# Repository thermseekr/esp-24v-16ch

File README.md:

# eumesmo-io-24v16ch
ESP32 based board with 16x optoisolated 24 VDC active high inputs, and 16x open collector 24 VDC outputs.

The outputs are based on the MMBT2222A SMD transistor and are rated for a maximum of 500mA, although it is recommended to limit the current to 350 mA for continous operation. If driving inductive loads like relays, a freewheeling diode or a snubber circuit should be used to limit the switching transients and protect the transistors.

Also included is a 1-Wire interface for external sensors. This interface can be switched to connect either to GPIO16 for use with a bitbang driver like the one available in Tasmota, or to a DS2482S-100 1-Wire master for building more complex networks. Selection is made via SW2, according to the description printed on the PCB. **Attention:** only one dip-switch can be on at any given time.

The board is compatible with the SP7 DIN rail system from [Metaltex](https://www.metaltex.com.br/).

## Hardware Specifications

| Feature | Specification |
| :--- | :--- |
| **Microcontroller** | ESP32-WROOM-32UE-N16 (16MB flash) |
| **Inputs** | 16x 24VDC (optoisolated, active high) |
| **Outputs** | 16x 24VDC (open collector, 350mA cont. / 500mA peak) |
| **Peripherals** | 1-Wire Interface, GPIO or 1-Wire master |
| **Form Factor** | Metaltex DIN Rail Compatible |

## VERSION HISTORY

V6.3 - 2026/07/02 - Added CPU health LED.

V6.2 - 2026/06/13 - Repository renamed from ESP-24V-16CH to eumesmo-io-24v16ch to align the design with the **eumesmo** line of building automation products.

V6.1 - 2026/06/09 - Added voltage monitors for the reset pins on the ESP32 and LAN8710A, replacing the RC circuits. The idea is to get more reliability on the power up sequence with a more controlled reset scheme and a sharper edge on the reset signal. For the ESP32 a TPS3820-33 was selected, which has a reset delay of 25ms. The LAN8710A received a TPS3823-33 with a 200ms delay. The sequence is: ESP32 gets power and goes out of reset 25ms after power good is detected at the 3V3 rail. After boot GPIO12 will go high enabling the 3V3LAN power rail and feeding power to both LAN8710A and TPS3823-33. Then, 200ms after power good is detected on the 3V3LAN rail, the LAN8710A will go out of reset and the power sequence is completed.

V6.0 - 2026/06/06 - The ESP32 was repositioned to allow for better routing to/from the PHY. Test points and a shunt resistor on the 5V rail were added to be used during tests. Will be remove in later versions. A separate GND plane and connector for optocouplers inputs was included. New ethernet connector, with tab up for easier integration with DIN holders from Metaltex. Connectors were replaced for 3.5mm pitch versions for easier wiring installation in the field. The board had to grow 10mm to accomodate these. SMD capacitor sizes were revised for better performance. Transistor base current for the ouputs was increased from 2,3mA to 5,5mA to ensure better saturation. Now, higher loads can be driven without the risk of putting the transistor in the active region. The MCP23017 expander for the inputs was replaced by 2x MCP23008 to avoid the infamous MCP23017 input bug. Rpacks were replaced for individual resistors for more flexible layout. Talking about layout, it was fully revised with better impedance matching for LAN8710 Tx/Rx signal traces. At last, the loads for 3V3A and 3V3LAN rails were revised.

V5.2 - 2026/02/10 - Pins GPA7 and GPB7 of the input MCP23017 were disabled as recommended by Microchip. Inputs 1 and 2 were assigned to GPIO34 and GPIO35 on the ESP32. The mentioned pins were pulled down to 0V and disabled on the mcp23x.dat template. Templates and GPIO assignment information on the schematics were updated.

V5.1 - Corrected footprint of R7 and repositioned the RESET switch as noted by [@yvkoch](https://github.com/yvkoch). Thanks Yrjö! Improved the 1-Wire bus interface aiming for cable runs up to 50m, still to be tested. Also included the option to connect a GPIO to the 1-Wire bus. ATENTION, SW2 can only have one switch ON at any given time, to connect either the DS2482 or GPIO16 to the 1-Wire bus.

V5.0 - Removed the onboard temperature sensor, too sensitive to be on a PCB and also measure the ambient temperature inside the cabinet. Even with cuts around the sensor, it was better at measuring each transistor's influence on the PCB's temperature than the temperature of the environment. Replaced the analog NTC inputs for a 1-Wire i2c interface. Mixing analog and digital circuits on a PCB requires more testing and developing time than I have available. So, fully digital we go. Decreased the brightness of the LEDs, maybe this time I'll get them right :) Repositioned components and rerouted the whole board following the valuable insights taken from [Phil's Lab](https://github.com/pms67) latest videos about Kicad. Thank you very much, Phil.

V4.1 - Redesigned NTC inputs for using differential mode for better immunity against noise. Also the low pass filters were redesigned, the original ones were pretty much useless for any cable larger that 2 meters.

V4.0 - Redesigned digital inputs for better tolerance to long cable runs in noisy environment. Removed pads for NTC inputs 3 and 4, tied them to GND.

V3.2 - Added 4 NTC inputs using an ADS1115 A/D converter with i2c. Reduced current on the LEDs, brightness was too high. Added series resistor and rerouted clock track for better impedance and ring control. Rerouted TX/RX and SCL/SDA tracks for improved signal quality. Layers reordered so the ground plane is directly below the top layer. Returned ESP32 to 16MB version.

V3.1 - Added AHT20 onboard temperature and humidity sensor for cabinet environment monitoring. Replaced ESP32 16MB for 4MB because no stock at JLCPCB.

V3 - Power LED moved to 5V bus. Individual resistors replaced for rpacks where applicable. Moved from 2 to 4 layers, board reduced 30mm in lenght. USB connector repositioned and replaced for horizontal version.

V2 - All GPIOs moved to MCP23017 expanders. MCP interrupt pins connected to GPIOs on the ESP32. USB connector changed for USB type C.

V1 - Initial version, not released. The first 8 inputs used native ESP32 GPIOs, other inputs and all outputs were wired through MCP GPIO expanders.

## LICENSE

This project is licensed under the [Creative Commons BY-NC 4.0 License](https://creativecommons.org/licenses/by-nc/4.0/).
Commercial use is not permitted without prior written consent. See the [LICENSE.txt](LICENSE.txt) file for details.

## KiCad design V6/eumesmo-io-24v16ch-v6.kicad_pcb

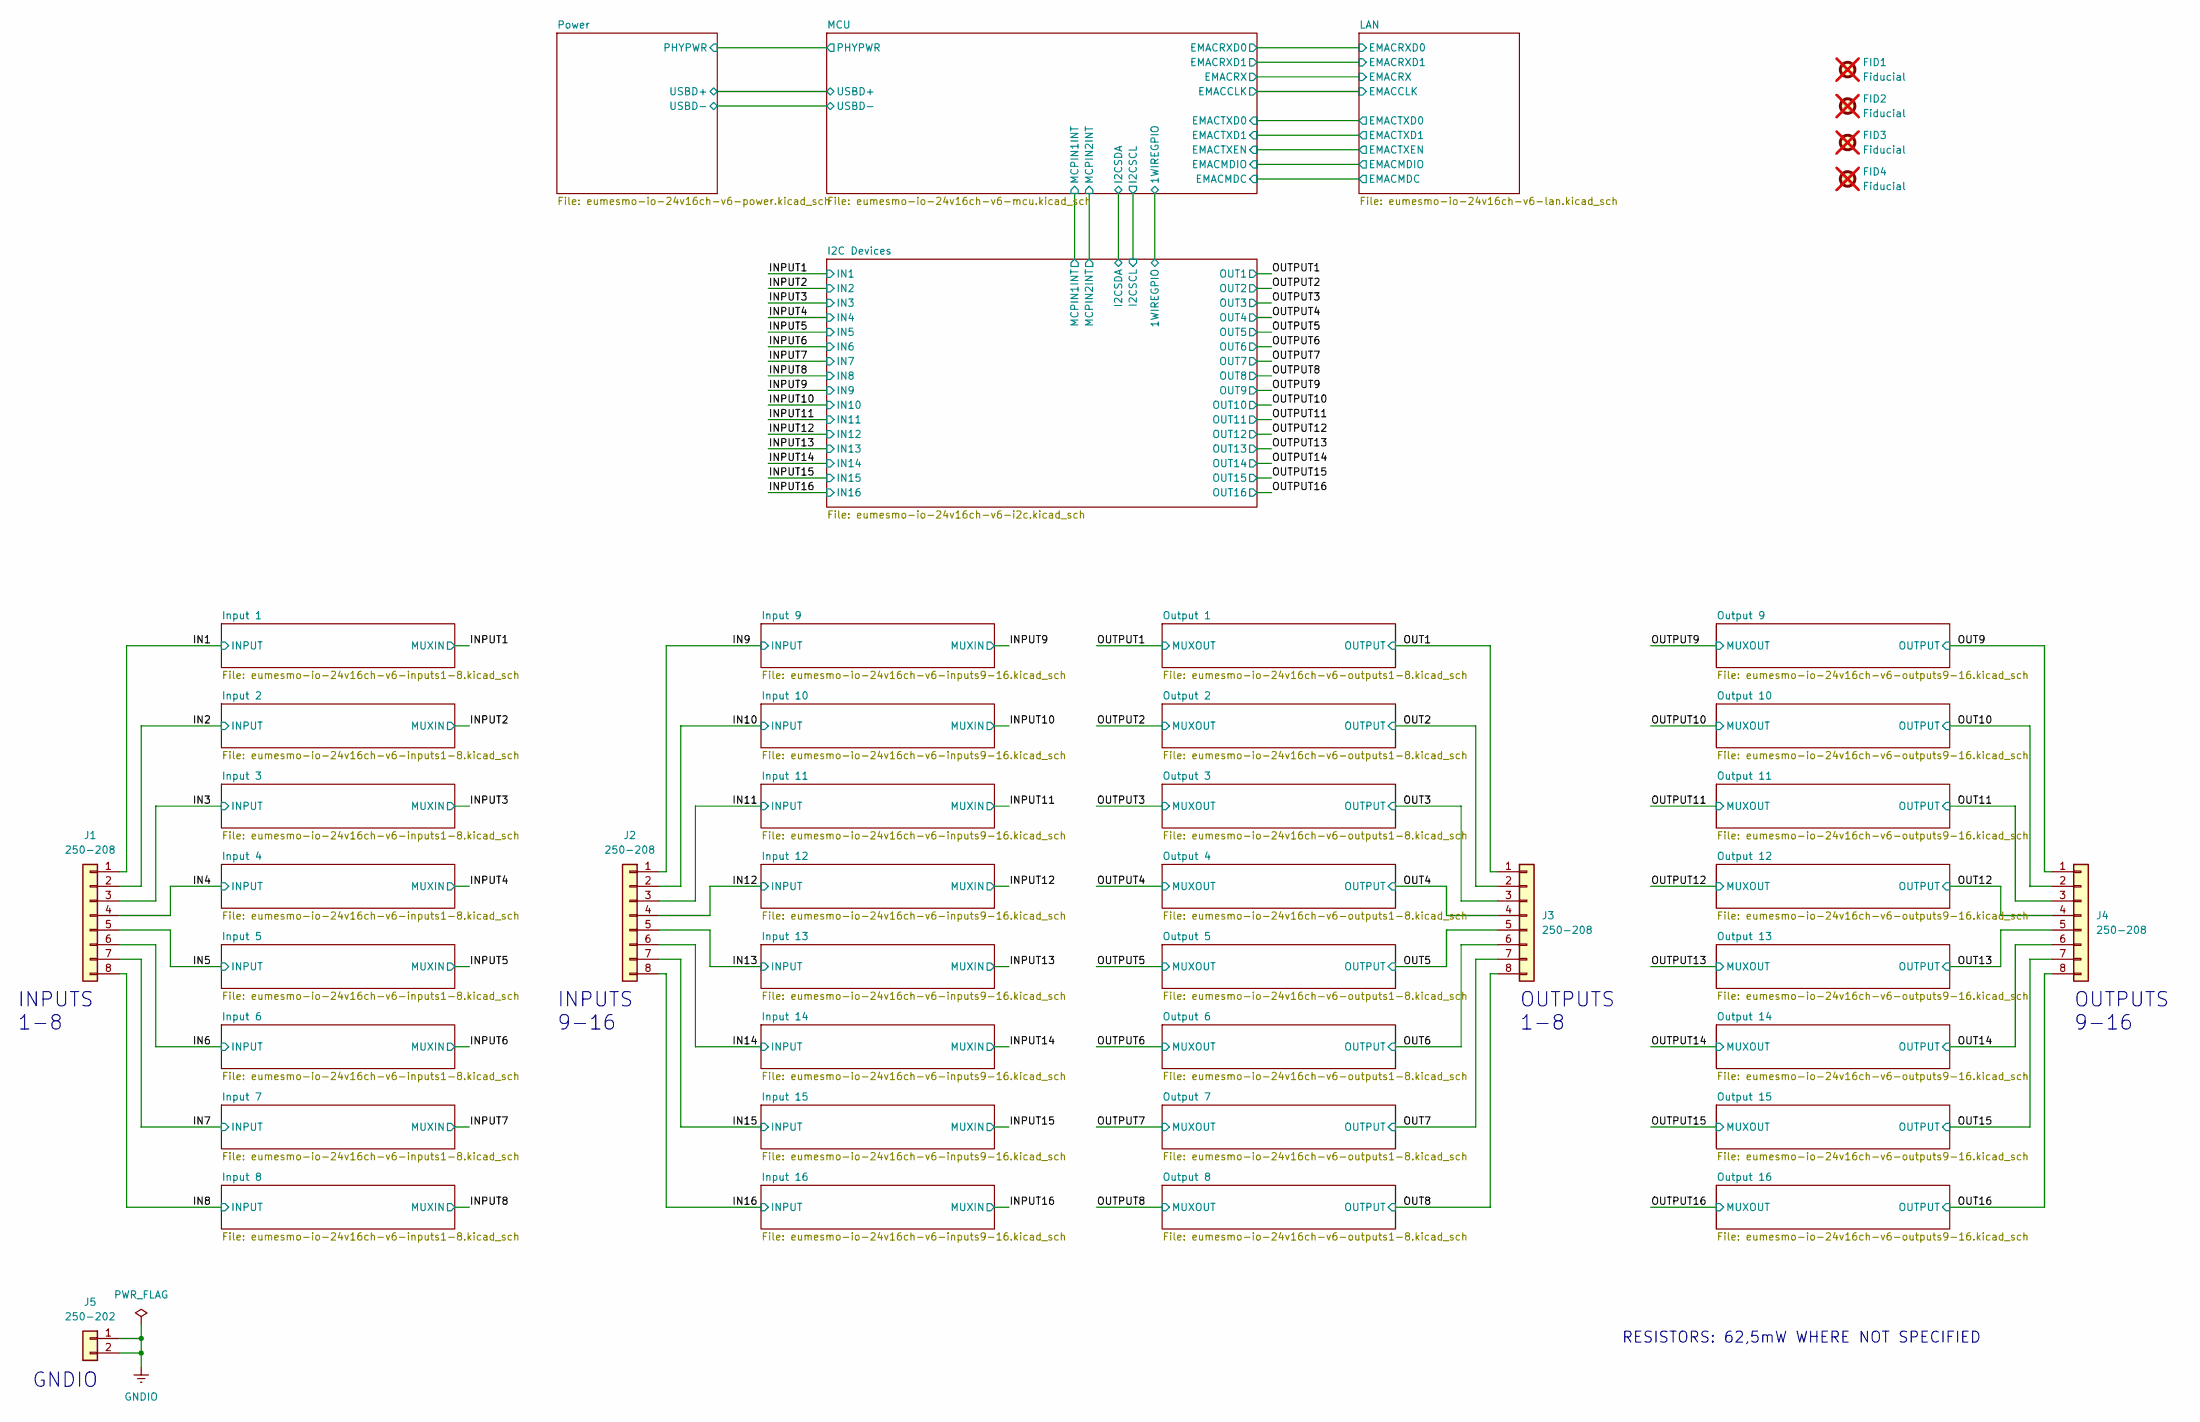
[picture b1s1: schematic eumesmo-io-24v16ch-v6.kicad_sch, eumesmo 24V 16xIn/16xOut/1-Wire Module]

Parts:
FID1, FID2, FID3, FID4: Fiducial; Fiducial_1mm_Mask2mm; not fitted
J1, J2, J3, J4: 250-208; TerminalBlock_Wago_250-208_1x08_P3.5mm_45Degree; Mfr PN 250-208; LCSC Part # C2833587
J5: 250-202; TerminalBlock_Wago_250-202_1x02_P3.5mm_45Degree; Mfr PN 250-202; LCSC Part # C2765061

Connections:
/IN1: J1.1; also elsewhere on the board
/IN2: J1.2; also elsewhere on the board
/IN3: J1.3; also elsewhere on the board
/IN4: J1.4; also elsewhere on the board
/IN5: J1.5; also elsewhere on the board
/IN6: J1.6; also elsewhere on the board
/IN7: J1.7; also elsewhere on the board
/IN8: J1.8; also elsewhere on the board
/IN9: J2.1; also elsewhere on the board
/IN10: J2.2; also elsewhere on the board
/IN11: J2.3; also elsewhere on the board
/IN12: J2.4; also elsewhere on the board
/IN13: J2.5; also elsewhere on the board
/IN14: J2.6; also elsewhere on the board
/IN15: J2.7; also elsewhere on the board
/IN16: J2.8; also elsewhere on the board
/OUT1: J3.1; also elsewhere on the board
/OUT2: J3.2; also elsewhere on the board
/OUT3: J3.3; also elsewhere on the board
/OUT4: J3.4; also elsewhere on the board
/OUT5: J3.5; also elsewhere on the board
/OUT6: J3.6; also elsewhere on the board
/OUT7: J3.7; also elsewhere on the board
/OUT8: J3.8; also elsewhere on the board
/OUT9: J4.1; also elsewhere on the board
/OUT10: J4.2; also elsewhere on the board
/OUT11: J4.3; also elsewhere on the board
/OUT12: J4.4; also elsewhere on the board
/OUT13: J4.5; also elsewhere on the board
/OUT14: J4.6; also elsewhere on the board
/OUT15: J4.7; also elsewhere on the board
/OUT16: J4.8; also elsewhere on the board
GNDIO: J5.1, J5.2; also elsewhere on the board

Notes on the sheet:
OUTPUTS 1-8
OUTPUTS 9-16
RESISTORS: 62,5mW WHERE NOT SPECIFIED
INPUTS 1-8
GNDIO
INPUTS 9-16

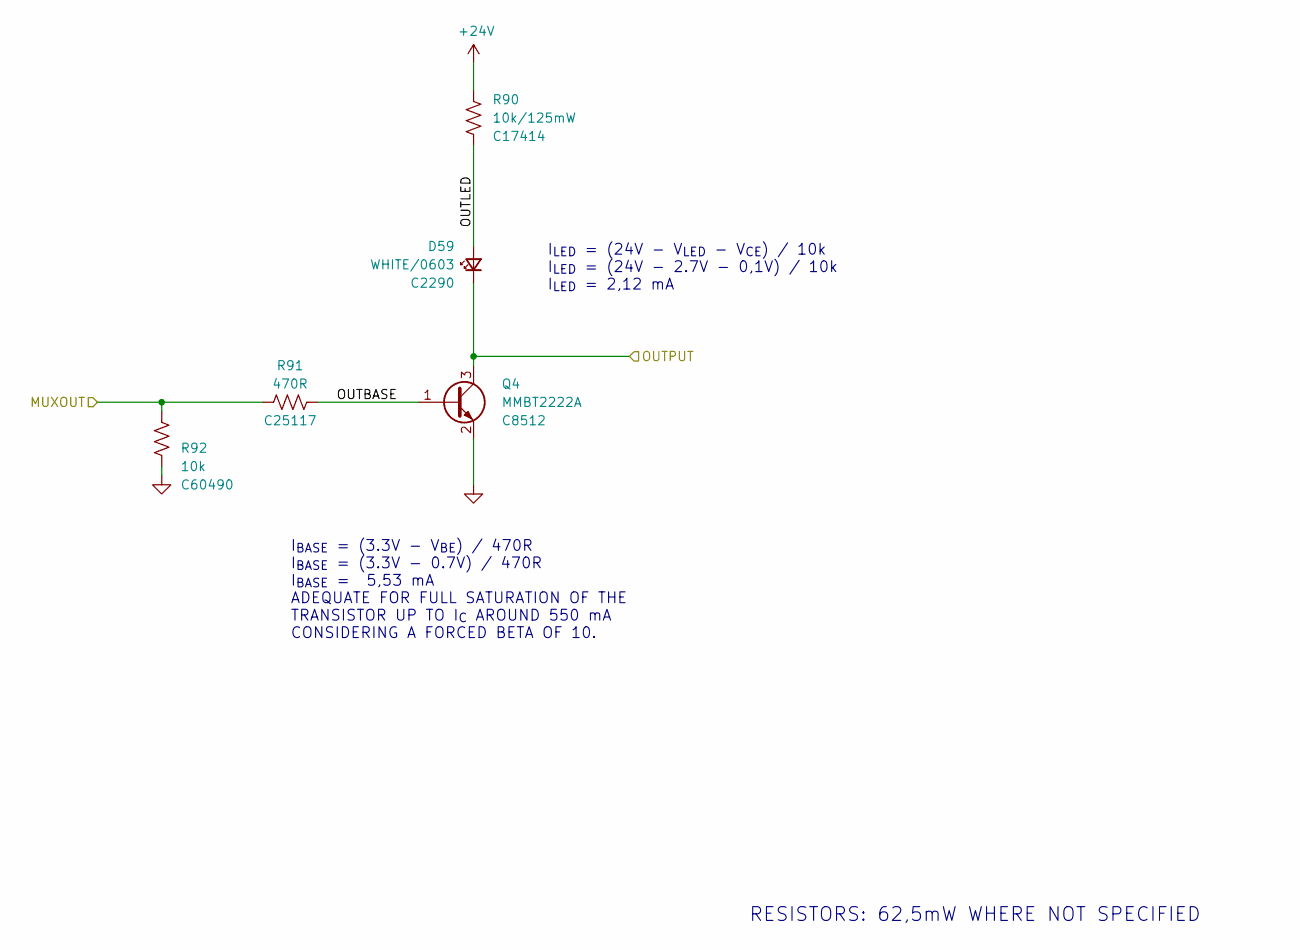
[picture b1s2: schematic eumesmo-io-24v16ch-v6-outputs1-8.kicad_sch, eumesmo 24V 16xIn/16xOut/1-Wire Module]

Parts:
D59: WHITE/0603; LED_0603_1608Metric; Mfr PN KT-0603W; LCSC Part # C2290
Q4: MMBT2222A; SOT-23-Narrow; Mfr PN MMBT2222A; LCSC Part # C8512
R90: 10k/125mW; R_0805_2012Metric; Mfr PN 0805W8F1002T5E; LCSC Part # C17414
R91: 470R; R_0402_1005Metric; Mfr PN 0402WGF4700TCE; LCSC Part # C25117
R92: 10k; R_0402_1005Metric; Mfr PN RC0402FR-0710KL; LCSC Part # C60490

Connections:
+24V: R90.1; also elsewhere on the board
/OUT1: D59.1 (K), Q4.3 (C); also elsewhere on the board
/OUTPUT1: R91.2, R92.2; also elsewhere on the board
/Output 1/OUTBASE: Q4.1 (B), R91.1
/Output 1/OUTLED: D59.2 (A), R90.2
GND: Q4.2 (E), R92.1; also elsewhere on the board

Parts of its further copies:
D60, D61, D62, D63, D64, D65, D66: WHITE/0603; LED_0603_1608Metric; Mfr PN KT-0603W; LCSC Part # C2290
Q5, Q6, Q7, Q8, Q9, Q10, Q11: MMBT2222A; SOT-23-Narrow; Mfr PN MMBT2222A; LCSC Part # C8512
R93, R96, R99, R102, R105, R108, R111: 10k/125mW; R_0805_2012Metric; Mfr PN 0805W8F1002T5E; LCSC Part # C17414
R94, R97, R100, R103, R106, R109, R112: 470R; R_0402_1005Metric; Mfr PN 0402WGF4700TCE; LCSC Part # C25117
R95, R98, R101, R104, R107, R110, R113: 10k; R_0402_1005Metric; Mfr PN RC0402FR-0710KL; LCSC Part # C60490

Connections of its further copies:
+24V: R93.1, R96.1, R99.1, R102.1, R105.1, R108.1, R111.1; also elsewhere on the board
/OUT2: D60.1 (K), Q5.3 (C); also elsewhere on the board
/OUT3: D61.1 (K), Q6.3 (C); also elsewhere on the board
/OUT4: D62.1 (K), Q7.3 (C); also elsewhere on the board
/OUT5: D63.1 (K), Q8.3 (C); also elsewhere on the board
/OUT6: D64.1 (K), Q9.3 (C); also elsewhere on the board
/OUT7: D65.1 (K), Q10.3 (C); also elsewhere on the board
/OUT8: D66.1 (K), Q11.3 (C); also elsewhere on the board
/OUTPUT2: R94.2, R95.2; also elsewhere on the board
/OUTPUT3: R97.2, R98.2; also elsewhere on the board
/OUTPUT4: R100.2, R101.2; also elsewhere on the board
/OUTPUT5: R103.2, R104.2; also elsewhere on the board
/OUTPUT6: R106.2, R107.2; also elsewhere on the board
/OUTPUT7: R109.2, R110.2; also elsewhere on the board
/OUTPUT8: R112.2, R113.2; also elsewhere on the board
/Output 2/OUTBASE: Q5.1 (B), R94.1
/Output 2/OUTLED: D60.2 (A), R93.2
/Output 3/OUTBASE: Q6.1 (B), R97.1
/Output 3/OUTLED: D61.2 (A), R96.2
/Output 4/OUTBASE: Q7.1 (B), R100.1
/Output 4/OUTLED: D62.2 (A), R99.2
/Output 5/OUTBASE: Q8.1 (B), R103.1
/Output 5/OUTLED: D63.2 (A), R102.2
/Output 6/OUTBASE: Q9.1 (B), R106.1
/Output 6/OUTLED: D64.2 (A), R105.2
/Output 7/OUTBASE: Q10.1 (B), R109.1
/Output 7/OUTLED: D65.2 (A), R108.2
/Output 8/OUTBASE: Q11.1 (B), R112.1
/Output 8/OUTLED: D66.2 (A), R111.2
GND: Q5.2 (E), Q6.2 (E), Q7.2 (E), Q8.2 (E), Q9.2 (E), Q10.2 (E), Q11.2 (E), R95.1, R98.1, R101.1, R104.1, R107.1, R110.1, R113.1; also elsewhere on the board

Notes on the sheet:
I_{LED} = (24V - V_{LED} - V_{CE}) / 10k I_{LED} = (24V - 2.7V - 0,1V) / 10k I_{LED} = 2,12 mA
RESISTORS: 62,5mW WHERE NOT SPECIFIED
I_{BASE} = (3.3V - V_{BE}) / 470R I_{BASE} = (3.3V - 0.7V) / 470R I_{BASE} = 5,53 mA ADEQUATE FOR FULL SATURATION OF THE TRANSISTOR UP TO I_{C} AROUND 550 mA CONSIDERING A FORCED BETA OF 10.

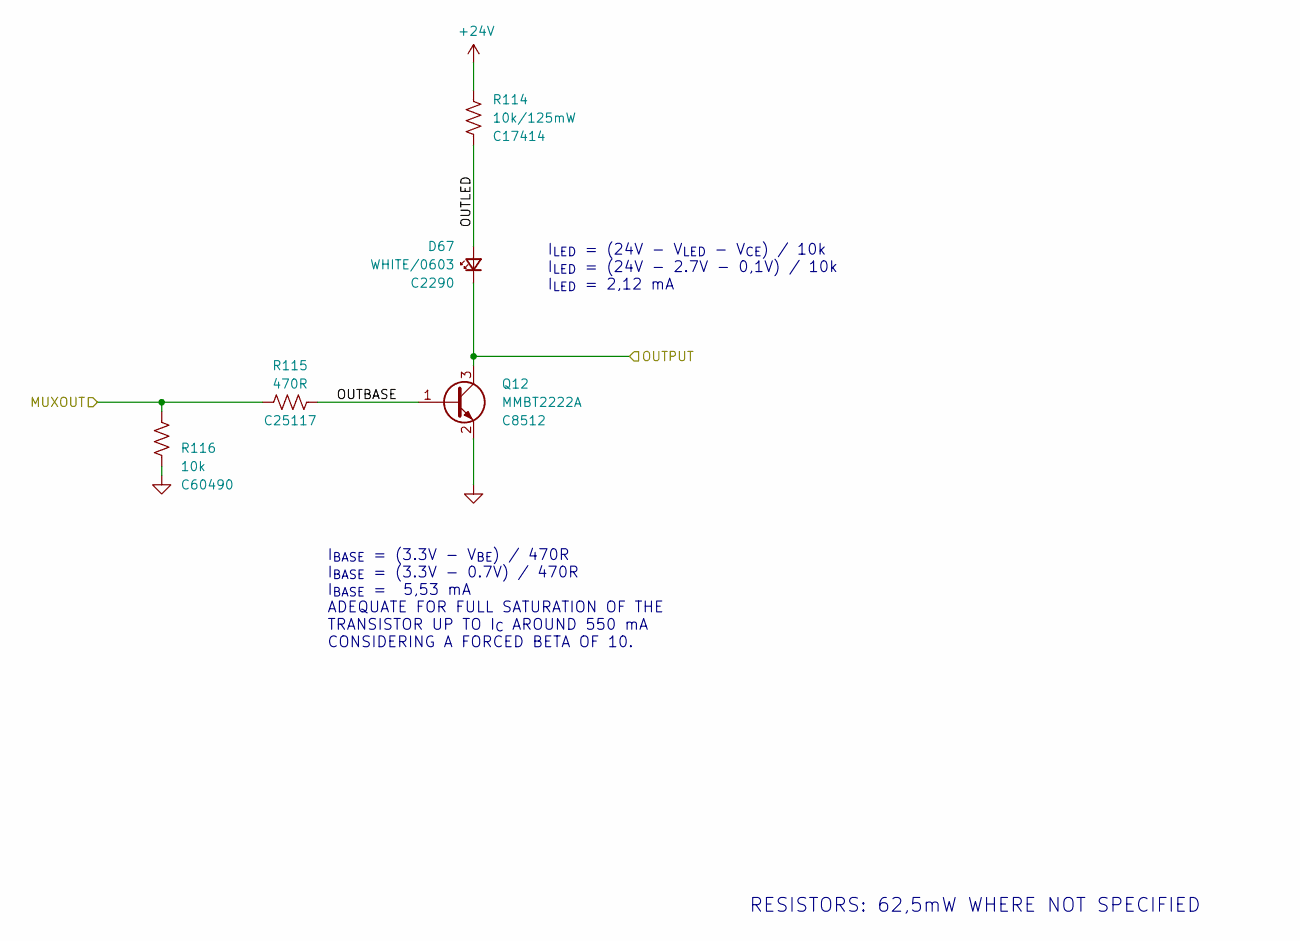
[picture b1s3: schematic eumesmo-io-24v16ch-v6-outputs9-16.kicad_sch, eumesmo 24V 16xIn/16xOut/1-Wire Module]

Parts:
D67: WHITE/0603; LED_0603_1608Metric; Mfr PN KT-0603W; LCSC Part # C2290
Q12: MMBT2222A; SOT-23-Narrow; Mfr PN MMBT2222A; LCSC Part # C8512
R114: 10k/125mW; R_0805_2012Metric; Mfr PN 0805W8F1002T5E; LCSC Part # C17414
R115: 470R; R_0402_1005Metric; Mfr PN 0402WGF4700TCE; LCSC Part # C25117
R116: 10k; R_0402_1005Metric; Mfr PN RC0402FR-0710KL; LCSC Part # C60490

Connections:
+24V: R114.1; also elsewhere on the board
/OUT9: D67.1 (K), Q12.3 (C); also elsewhere on the board
/OUTPUT9: R115.2, R116.2; also elsewhere on the board
/Output 9/OUTBASE: Q12.1 (B), R115.1
/Output 9/OUTLED: D67.2 (A), R114.2
GND: Q12.2 (E), R116.1; also elsewhere on the board

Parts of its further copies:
D68, D69, D70, D71, D72, D73, D74: WHITE/0603; LED_0603_1608Metric; Mfr PN KT-0603W; LCSC Part # C2290
Q13, Q14, Q15, Q16, Q17, Q18, Q19: MMBT2222A; SOT-23-Narrow; Mfr PN MMBT2222A; LCSC Part # C8512
R117, R120, R123, R126, R129, R132, R135: 10k/125mW; R_0805_2012Metric; Mfr PN 0805W8F1002T5E; LCSC Part # C17414
R118, R121, R124, R127, R130, R133, R136: 470R; R_0402_1005Metric; Mfr PN 0402WGF4700TCE; LCSC Part # C25117
R119, R122, R125, R128, R131, R134, R137: 10k; R_0402_1005Metric; Mfr PN RC0402FR-0710KL; LCSC Part # C60490

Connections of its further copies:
+24V: R117.1, R120.1, R123.1, R126.1, R129.1, R132.1, R135.1; also elsewhere on the board
/OUT10: D68.1 (K), Q13.3 (C); also elsewhere on the board
/OUT11: D69.1 (K), Q14.3 (C); also elsewhere on the board
/OUT12: D70.1 (K), Q15.3 (C); also elsewhere on the board
/OUT13: D71.1 (K), Q16.3 (C); also elsewhere on the board
/OUT14: D72.1 (K), Q17.3 (C); also elsewhere on the board
/OUT15: D73.1 (K), Q18.3 (C); also elsewhere on the board
/OUT16: D74.1 (K), Q19.3 (C); also elsewhere on the board
/OUTPUT10: R118.2, R119.2; also elsewhere on the board
/OUTPUT11: R121.2, R122.2; also elsewhere on the board
/OUTPUT12: R124.2, R125.2; also elsewhere on the board
/OUTPUT13: R127.2, R128.2; also elsewhere on the board
/OUTPUT14: R130.2, R131.2; also elsewhere on the board
/OUTPUT15: R133.2, R134.2; also elsewhere on the board
/OUTPUT16: R136.2, R137.2; also elsewhere on the board
/Output 10/OUTBASE: Q13.1 (B), R118.1
/Output 10/OUTLED: D68.2 (A), R117.2
/Output 11/OUTBASE: Q14.1 (B), R121.1
/Output 11/OUTLED: D69.2 (A), R120.2
/Output 12/OUTBASE: Q15.1 (B), R124.1
/Output 12/OUTLED: D70.2 (A), R123.2
/Output 13/OUTBASE: Q16.1 (B), R127.1
/Output 13/OUTLED: D71.2 (A), R126.2
/Output 14/OUTBASE: Q17.1 (B), R130.1
/Output 14/OUTLED: D72.2 (A), R129.2
/Output 15/OUTBASE: Q18.1 (B), R133.1
/Output 15/OUTLED: D73.2 (A), R132.2
/Output 16/OUTBASE: Q19.1 (B), R136.1
/Output 16/OUTLED: D74.2 (A), R135.2
GND: Q13.2 (E), Q14.2 (E), Q15.2 (E), Q16.2 (E), Q17.2 (E), Q18.2 (E), Q19.2 (E), R119.1, R122.1, R125.1, R128.1, R131.1, R134.1, R137.1; also elsewhere on the board

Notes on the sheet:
RESISTORS: 62,5mW WHERE NOT SPECIFIED
I_{BASE} = (3.3V - V_{BE}) / 470R I_{BASE} = (3.3V - 0.7V) / 470R I_{BASE} = 5,53 mA ADEQUATE FOR FULL SATURATION OF THE TRANSISTOR UP TO I_{C} AROUND 550 mA CONSIDERING A FORCED BETA OF 10.
I_{LED} = (24V - V_{LED} - V_{CE}) / 10k I_{LED} = (24V - 2.7V - 0,1V) / 10k I_{LED} = 2,12 mA

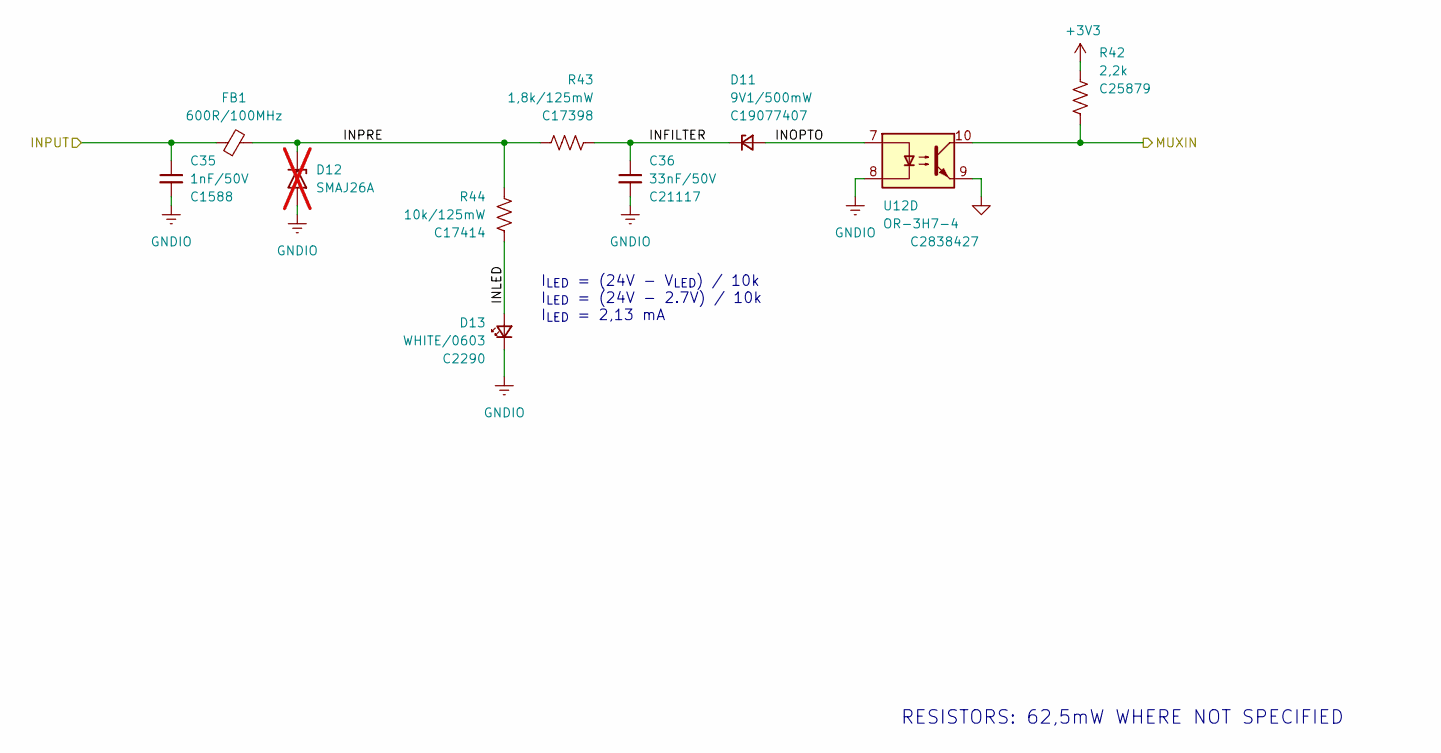
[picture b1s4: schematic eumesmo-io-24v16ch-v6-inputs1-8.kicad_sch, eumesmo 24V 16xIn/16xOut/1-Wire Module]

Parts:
C35: 1nF/50V; C_0603_1608Metric; Mfr PN CL10B102KB8NNNC; LCSC Part # C1588
C36: 33nF/50V; C_0603_1608Metric; Mfr PN CL10B333KB8NNNC; LCSC Part # C21117
D11: 9V1/500mW; D_SOD-123; Mfr PN BZT52C9V1; LCSC Part # C19077407
D12: SMAJ26A; D_SMA; Mfr PN SMAJ26A; LCSC Part # C19077543; not fitted
D13: WHITE/0603; LED_0603_1608Metric; Mfr PN KT-0603W; LCSC Part # C2290
FB1: 600R/100MHz; R_0603_1608Metric; Mfr PN BLM18KG601SN1D; LCSC Part # C85833
R42: 2,2k; R_0402_1005Metric; Mfr PN 0402WGF2201TCE; LCSC Part # C25879
R43: 1,8k/125mW; R_0805_2012Metric; Mfr PN 0805W8F1801T5E; LCSC Part # C17398
R44: 10k/125mW; R_0805_2012Metric; Mfr PN 0805W8F1002T5E; LCSC Part # C17414
U12: OR-3H7-4; SOP-16_4.4x10.4mm_P1.27mm; Mfr PN OR-3H7-4GB-TA1-G; LCSC Part # C2838427

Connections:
+3V3: R42.1; also elsewhere on the board
/IN1: C35.1, FB1.1; also elsewhere on the board
/INPUT1: R42.2, U12.10; also elsewhere on the board
/INPUT2: U12.12; also elsewhere on the board
/INPUT3: U12.14; also elsewhere on the board
/INPUT4: U12.16; also elsewhere on the board
/Input 1/INFILTER: C36.1, D11.1 (K), R43.1
/Input 1/INLED: D13.2 (A), R44.2
/Input 1/INOPTO: D11.2 (A), U12.7
/Input 1/INPRE: FB1.2, R43.2, R44.1
/Input 2/INOPTO: U12.5; also elsewhere on the board
/Input 3/INOPTO: U12.3; also elsewhere on the board
/Input 4/INOPTO: U12.1; also elsewhere on the board
GND: U12.9, U12.11, U12.13, U12.15; also elsewhere on the board
GNDIO: C35.2, C36.2, D12.2 (A2), D13.1 (K), U12.2, U12.4, U12.6, U12.8; also elsewhere on the board

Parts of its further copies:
C37, C39, C41, C43, C45, C47, C49: 1nF/50V; C_0603_1608Metric; Mfr PN CL10B102KB8NNNC; LCSC Part # C1588
C38, C40, C42, C44, C46, C48, C50: 33nF/50V; C_0603_1608Metric; Mfr PN CL10B333KB8NNNC; LCSC Part # C21117
D14, D17, D20, D23, D26, D29, D32: 9V1/500mW; D_SOD-123; Mfr PN BZT52C9V1; LCSC Part # C19077407
D16, D19, D22, D25, D28, D31, D34: WHITE/0603; LED_0603_1608Metric; Mfr PN KT-0603W; LCSC Part # C2290
FB2, FB3, FB4, FB5, FB6, FB7, FB8: 600R/100MHz; R_0603_1608Metric; Mfr PN BLM18KG601SN1D; LCSC Part # C85833
R45, R48, R51, R54, R57, R60, R63: 2,2k; R_0402_1005Metric; Mfr PN 0402WGF2201TCE; LCSC Part # C25879
R46, R49, R52, R55, R58, R61, R64: 1,8k/125mW; R_0805_2012Metric; Mfr PN 0805W8F1801T5E; LCSC Part # C17398
R47, R50, R53, R56, R59, R62, R65: 10k/125mW; R_0805_2012Metric; Mfr PN 0805W8F1002T5E; LCSC Part # C17414
U13: OR-3H7-4; SOP-16_4.4x10.4mm_P1.27mm; Mfr PN OR-3H7-4GB-TA1-G; LCSC Part # C2838427

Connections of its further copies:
+3V3: R45.1, R48.1, R51.1, R54.1, R57.1, R60.1, R63.1; also elsewhere on the board
/IN2: C37.1, FB2.1; also elsewhere on the board
/IN3: C39.1, FB3.1; also elsewhere on the board
/IN4: C41.1, FB4.1; also elsewhere on the board
/IN5: C43.1, FB5.1; also elsewhere on the board
/IN6: C45.1, FB6.1; also elsewhere on the board
/IN7: C47.1, FB7.1; also elsewhere on the board
/IN8: C49.1, FB8.1; also elsewhere on the board
/INPUT2: R45.2; also elsewhere on the board
/INPUT3: R48.2; also elsewhere on the board
/INPUT4: R51.2; also elsewhere on the board
/INPUT5: R54.2, U13.10; also elsewhere on the board
/INPUT6: R57.2, U13.12; also elsewhere on the board
/INPUT7: R60.2, U13.14; also elsewhere on the board
/INPUT8: R63.2, U13.16; also elsewhere on the board
/Input 2/INFILTER: C38.1, D14.1 (K), R46.1
/Input 2/INLED: D16.2 (A), R47.2
/Input 2/INOPTO: D14.2 (A); also elsewhere on the board
/Input 2/INPRE: FB2.2, R46.2, R47.1
/Input 3/INFILTER: C40.1, D17.1 (K), R49.1
/Input 3/INLED: D19.2 (A), R50.2
/Input 3/INOPTO: D17.2 (A); also elsewhere on the board
/Input 3/INPRE: FB3.2, R49.2, R50.1
/Input 4/INFILTER: C42.1, D20.1 (K), R52.1
/Input 4/INLED: D22.2 (A), R53.2
/Input 4/INOPTO: D20.2 (A); also elsewhere on the board
/Input 4/INPRE: FB4.2, R52.2, R53.1
/Input 5/INFILTER: C44.1, D23.1 (K), R55.1
/Input 5/INLED: D25.2 (A), R56.2
/Input 5/INOPTO: D23.2 (A), U13.7
/Input 5/INPRE: FB5.2, R55.2, R56.1
/Input 6/INFILTER: C46.1, D26.1 (K), R58.1
/Input 6/INLED: D28.2 (A), R59.2
/Input 6/INOPTO: D26.2 (A), U13.5
/Input 6/INPRE: FB6.2, R58.2, R59.1
/Input 7/INFILTER: C48.1, D29.1 (K), R61.1
/Input 7/INLED: D31.2 (A), R62.2
/Input 7/INOPTO: D29.2 (A), U13.3
/Input 7/INPRE: FB7.2, R61.2, R62.1
/Input 8/INFILTER: C50.1, D32.1 (K), R64.1
/Input 8/INLED: D34.2 (A), R65.2
/Input 8/INOPTO: D32.2 (A), U13.1
/Input 8/INPRE: FB8.2, R64.2, R65.1
GND: U13.9, U13.11, U13.13, U13.15; also elsewhere on the board
GNDIO: C37.2, C38.2, C39.2, C40.2, C41.2, C42.2, C43.2, C44.2, C45.2, C46.2, C47.2, C48.2, C49.2, C50.2, D16.1 (K), D19.1 (K), D22.1 (K), D25.1 (K), D28.1 (K), D31.1 (K), D34.1 (K), U13.2, U13.4, U13.6, U13.8; also elsewhere on the board

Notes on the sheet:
I_{LED} = (24V - V_{LED}) / 10k I_{LED} = (24V - 2.7V) / 10k I_{LED} = 2,13 mA
RESISTORS: 62,5mW WHERE NOT SPECIFIED

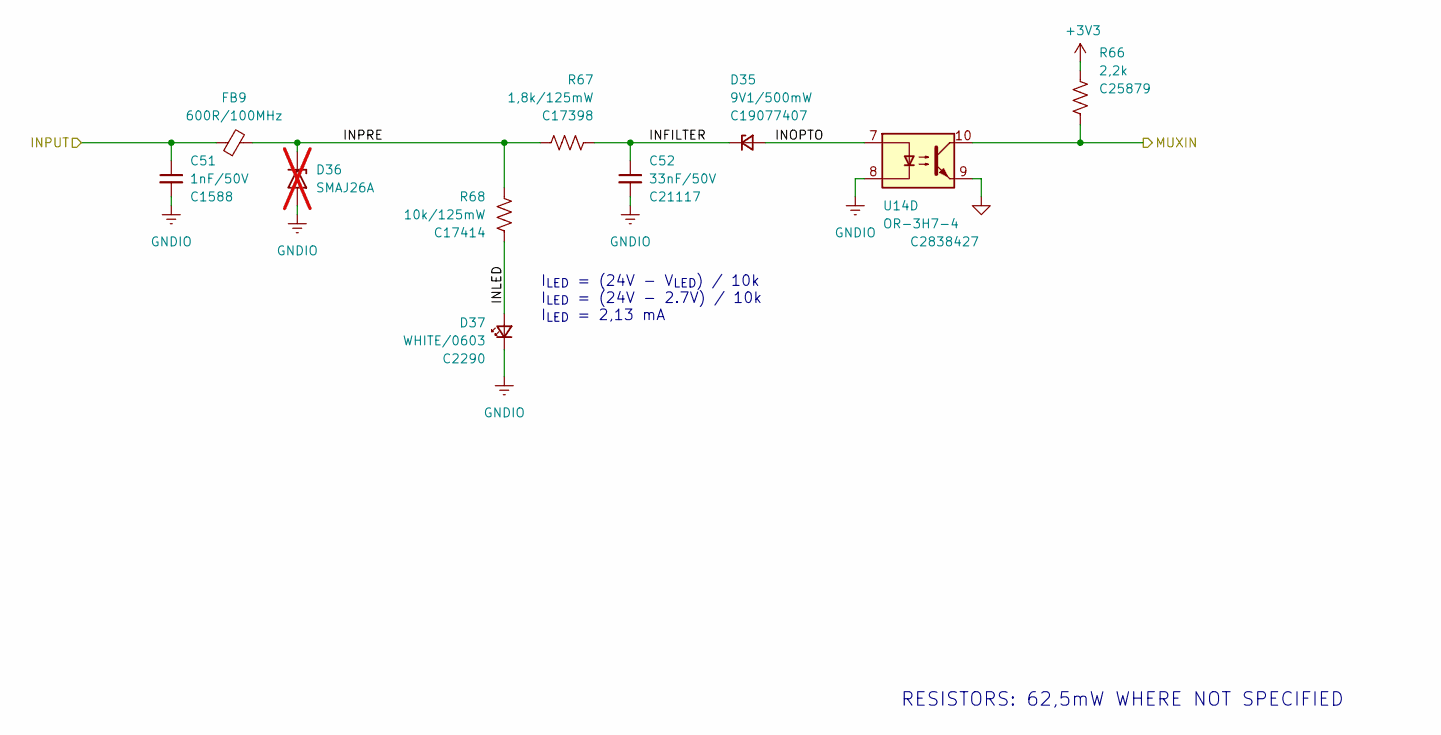
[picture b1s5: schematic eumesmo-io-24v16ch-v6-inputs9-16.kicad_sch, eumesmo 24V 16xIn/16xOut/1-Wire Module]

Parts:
C51: 1nF/50V; C_0603_1608Metric; Mfr PN CL10B102KB8NNNC; LCSC Part # C1588
C52: 33nF/50V; C_0603_1608Metric; Mfr PN CL10B333KB8NNNC; LCSC Part # C21117
D35: 9V1/500mW; D_SOD-123; Mfr PN BZT52C9V1; LCSC Part # C19077407
D36: SMAJ26A; D_SMA; Mfr PN SMAJ26A; LCSC Part # C19077543; not fitted
D37: WHITE/0603; LED_0603_1608Metric; Mfr PN KT-0603W; LCSC Part # C2290
FB9: 600R/100MHz; R_0603_1608Metric; Mfr PN BLM18KG601SN1D; LCSC Part # C85833
R66: 2,2k; R_0402_1005Metric; Mfr PN 0402WGF2201TCE; LCSC Part # C25879
R67: 1,8k/125mW; R_0805_2012Metric; Mfr PN 0805W8F1801T5E; LCSC Part # C17398
R68: 10k/125mW; R_0805_2012Metric; Mfr PN 0805W8F1002T5E; LCSC Part # C17414
U14: OR-3H7-4; SOP-16_4.4x10.4mm_P1.27mm; Mfr PN OR-3H7-4GB-TA1-G; LCSC Part # C2838427

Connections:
+3V3: R66.1; also elsewhere on the board
/IN9: C51.1, FB9.1; also elsewhere on the board
/INPUT9: R66.2, U14.10; also elsewhere on the board
/INPUT10: U14.12; also elsewhere on the board
/INPUT11: U14.14; also elsewhere on the board
/INPUT12: U14.16; also elsewhere on the board
/Input 9/INFILTER: C52.1, D35.1 (K), R67.1
/Input 9/INLED: D37.2 (A), R68.2
/Input 9/INOPTO: D35.2 (A), U14.7
/Input 9/INPRE: FB9.2, R67.2, R68.1
/Input 10/INOPTO: U14.5; also elsewhere on the board
/Input 11/INOPTO: U14.3; also elsewhere on the board
/Input 12/INOPTO: U14.1; also elsewhere on the board
GND: U14.9, U14.11, U14.13, U14.15; also elsewhere on the board
GNDIO: C51.2, C52.2, D36.2 (A2), D37.1 (K), U14.2, U14.4, U14.6, U14.8; also elsewhere on the board

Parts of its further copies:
C53, C55, C57, C59, C61, C63, C65: 1nF/50V; C_0603_1608Metric; Mfr PN CL10B102KB8NNNC; LCSC Part # C1588
C54, C56, C58, C60, C62, C64, C66: 33nF/50V; C_0603_1608Metric; Mfr PN CL10B333KB8NNNC; LCSC Part # C21117
D38, D41, D44, D47, D50, D53, D56: 9V1/500mW; D_SOD-123; Mfr PN BZT52C9V1; LCSC Part # C19077407
D40, D43, D46, D49, D52, D55, D58: WHITE/0603; LED_0603_1608Metric; Mfr PN KT-0603W; LCSC Part # C2290
FB10, FB11, FB12, FB13, FB14, FB15, FB16: 600R/100MHz; R_0603_1608Metric; Mfr PN BLM18KG601SN1D; LCSC Part # C85833
R69, R72, R75, R78, R81, R84, R87: 2,2k; R_0402_1005Metric; Mfr PN 0402WGF2201TCE; LCSC Part # C25879
R70, R73, R76, R79, R82, R85, R88: 1,8k/125mW; R_0805_2012Metric; Mfr PN 0805W8F1801T5E; LCSC Part # C17398
R71, R74, R77, R80, R83, R86, R89: 10k/125mW; R_0805_2012Metric; Mfr PN 0805W8F1002T5E; LCSC Part # C17414
U15: OR-3H7-4; SOP-16_4.4x10.4mm_P1.27mm; Mfr PN OR-3H7-4GB-TA1-G; LCSC Part # C2838427

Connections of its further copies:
+3V3: R69.1, R72.1, R75.1, R78.1, R81.1, R84.1, R87.1; also elsewhere on the board
/IN10: C53.1, FB10.1; also elsewhere on the board
/IN11: C55.1, FB11.1; also elsewhere on the board
/IN12: C57.1, FB12.1; also elsewhere on the board
/IN13: C59.1, FB13.1; also elsewhere on the board
/IN14: C61.1, FB14.1; also elsewhere on the board
/IN15: C63.1, FB15.1; also elsewhere on the board
/IN16: C65.1, FB16.1; also elsewhere on the board
/INPUT10: R69.2; also elsewhere on the board
/INPUT11: R72.2; also elsewhere on the board
/INPUT12: R75.2; also elsewhere on the board
/INPUT13: R78.2, U15.10; also elsewhere on the board
/INPUT14: R81.2, U15.12; also elsewhere on the board
/INPUT15: R84.2, U15.14; also elsewhere on the board
/INPUT16: R87.2, U15.16; also elsewhere on the board
/Input 10/INFILTER: C54.1, D38.1 (K), R70.1
/Input 10/INLED: D40.2 (A), R71.2
/Input 10/INOPTO: D38.2 (A); also elsewhere on the board
/Input 10/INPRE: FB10.2, R70.2, R71.1
/Input 11/INFILTER: C56.1, D41.1 (K), R73.1
/Input 11/INLED: D43.2 (A), R74.2
/Input 11/INOPTO: D41.2 (A); also elsewhere on the board
/Input 11/INPRE: FB11.2, R73.2, R74.1
/Input 12/INFILTER: C58.1, D44.1 (K), R76.1
/Input 12/INLED: D46.2 (A), R77.2
/Input 12/INOPTO: D44.2 (A); also elsewhere on the board
/Input 12/INPRE: FB12.2, R76.2, R77.1
/Input 13/INFILTER: C60.1, D47.1 (K), R79.1
/Input 13/INLED: D49.2 (A), R80.2
/Input 13/INOPTO: D47.2 (A), U15.7
/Input 13/INPRE: FB13.2, R79.2, R80.1
/Input 14/INFILTER: C62.1, D50.1 (K), R82.1
/Input 14/INLED: D52.2 (A), R83.2
/Input 14/INOPTO: D50.2 (A), U15.5
/Input 14/INPRE: FB14.2, R82.2, R83.1
/Input 15/INFILTER: C64.1, D53.1 (K), R85.1
/Input 15/INLED: D55.2 (A), R86.2
/Input 15/INOPTO: D53.2 (A), U15.3
/Input 15/INPRE: FB15.2, R85.2, R86.1
/Input 16/INFILTER: C66.1, D56.1 (K), R88.1
/Input 16/INLED: D58.2 (A), R89.2
/Input 16/INOPTO: D56.2 (A), U15.1
/Input 16/INPRE: FB16.2, R88.2, R89.1
GND: U15.9, U15.11, U15.13, U15.15; also elsewhere on the board
GNDIO: C53.2, C54.2, C55.2, C56.2, C57.2, C58.2, C59.2, C60.2, C61.2, C62.2, C63.2, C64.2, C65.2, C66.2, D40.1 (K), D43.1 (K), D46.1 (K), D49.1 (K), D52.1 (K), D55.1 (K), D58.1 (K), U15.2, U15.4, U15.6, U15.8; also elsewhere on the board

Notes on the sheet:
I_{LED} = (24V - V_{LED}) / 10k I_{LED} = (24V - 2.7V) / 10k I_{LED} = 2,13 mA
RESISTORS: 62,5mW WHERE NOT SPECIFIED
